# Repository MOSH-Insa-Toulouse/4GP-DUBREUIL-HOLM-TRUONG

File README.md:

# 4GP-DUBREUIL-HOLM-TRUONG

## SMOMAIRE
- [I) Présentation](#Présentation)
- [II) Matériel necessaire](#Matériel-necessaire)
   - [Software](#Software)
   - [Hardware](#Hardware)
- [III)Livrables](#Livrables)
   - [1) Simulation LtSpice](#Simulation-LtSpice)
   - [2) Conception PCB avec KiCad](#Conception-PCB-avec-KiCad)
   - [3) Code Arduino](#Code-Arduino)
   - [4) Application Android avec MITApp Inventor](#Application-Android-avec-MITApp-Inventor)
   - [5) Réalisation Physique du Circuit](#Réalisation-Physique-du-Circuit)
   - [6) Banc de Test Expérimental](#Banc-de-Test-Expérimental)
- [IV)Gestion de projet](#gestion-projet)
   - [1)Répartition du travail](#repartition-travail)
   - [2) Contacts](#contacts)

## I) Présentation
Ce répertoire présente l'ensemble des éléments nécessaire à la conception d'un capteur de pression en graphite réalisé dans le cadre de l'UF I4GPMH21 : Du capteur au banc de test en open source hardware.
L’objectif était de concevoir un dispositif de mesure de déformation utilisant un capteur innovant, low-tech, basé sur du graphite appliqué sur papier, selon le principe décrit dans l’article scientifique :  
**"Pencil Drawn Strain Gauges and Chemiresistors on Paper"** (Cheng-Wei Lin, Zhibo Zhao, Jaemyung Kim & Jiaxing Huang). Ce capteur, d'une simplicité remarquable, est constitué d'un morceau de papier sur lequel du graphite est appliqué à l'aide d'un crayon à papier.

Le principe de fonctionnement repose sur l'observation que la déformation du papier entraîne une variation du nombre de particules de graphite interconnectées. Cette modification de la structure granulaire du graphite se traduit par une variation de la résistance et de la conductance du capteur. En exploitant cette propriété, il devient possible de remonter à la déformation subie, à l'instar d'une jauge de contrainte classique.

Le fonctionnement repose sur la variation de la conductivité électrique du graphite en fonction de la contrainte mécanique appliquée au support papier. Ce phénomène permet de mesurer la déformation avec une technologie simple, accessible et écologique.
## II) Matériel necessaire
### ***Software*** (Présenté dans l'ordre d'utilisation)
1. LtSpice : Logiciel permettant la modélisation et simulation des circuits électroniques. 
1. KiCad : Logiciel permettant le développement et conception du PCB (*Printed Board Circuit*)
1. Arduino IDE : IDE utilisé pour écrire le code du micro-contrôleur Arduino. 
1. MITApp Inventor : WebService pour le développement d'une application Android.
### ***Hardware***
1. Micro-contrôleur Arduino UNO
1. Modules 
    * Bluetooth HC-05
    * Capteur de déformation en graphite
    * Capteur de déformation du commerce
    * Écran OLED
    * Encodeur Rotatoire
    * Potentiomètre digital
    * Servo-Moteur
1. Banc de test réalisé à l'imprimante 3D

## III) Livrables
### 1) Simulation LtSpice

Un montage à transimpédance a été conçu afin d'amplifier le faible courant produit par le capteur graphite. Ce montage utilise un amplificateur opérationnel de précision (LTC1050) pour convertir le courant en tension, compatible avec les entrées analogiques d’un Arduino UNO.  

Trois filtres passe-bas ont été intégrés pour minimiser le bruit :
- Un filtre passe-bas passif (R1, C1) à l'entrée : filtre RC à 16 Hz pour réduire les perturbations en courant,
- Un filtre passe-bas actif (R3, C4) couplé à l'AOP : filtre actif à 1,6 Hz pour éliminer le bruit secteur (50 Hz),
- Un filtre passe-bas (R5, C2) à la sortie de l'AOP : filtre à 1,6 kHz pour lisser le signal final.

Des simulations transitoires et fréquentielles ont validé l’amplification et l’efficacité de la filtration (atténuation > 70 dB à 50 Hz).

#### ***Graphique***

#### ***Schéma du montage***

### 2) Conception PCB avec KiCad

Dans cette section, nous présentons le processus de conception du circuit imprimé du projet, allant de la simulation électrique à la modélisation 3D, en passant par le routage des composants. L’objectif est de réaliser une carte fonctionnelle permettant l’acquisition, le traitement et la transmission du signal mesuré par le capteur graphite.

### Étape 1 : Sélection et intégration des composants

Le circuit est conçu pour intégrer et connecter plusieurs composants essentiels à l’Arduino :

- Amplificateur opérationnel **LT1050** (amplification analogique du signal capteur)
- **Servomoteur** 
- **Potentiomètre numérique** (ajustement dynamique de gain)
- **Encodeur rotatoire**
- **Écran OLED**
- **Module Bluetooth HC-05** (communication sans fil avec une application mobile)
- Deux broches dédiées au **capteur graphène**

L’ensemble des connexions logiques et électriques est établi dans le schéma du PCB sur KiCad pour s'assurer de la compatibilité avec l’Arduino.

### Étape 2 : Simulation du schéma électrique

La conception a débuté par la création d’un schéma électrique simulé sous **LTspice**. Cette simulation permet de valider le comportement du circuit d’amplification, notamment autour de l’amplificateur opérationnel **LT 1050**, qui joue un rôle essentiel dans l’amplification du signal analogique issu du capteur graphite.

Une fois le schéma validé, il est reproduit dans **KiCad** afin de préparer la conception physique du circuit.

#### ***Schematic***

Ici sont présenté les différents éléments qui composeront le *shield* de notre projet ainsi que l'assignation des différentes connexions. On y retrouve en haut à droite l'ensemble des pins de connexion de l'arduino, à gauche, le schéma de l'amplificateur ainsi que la connexion du capteur graphène. Enfin, en bas, on retrouve la schématisation des différents modules à intégrer.

### Étape 3 : Routage PCB dans KiCad

La phase suivante consiste à réaliser le **routage** du circuit. Cela implique de placer les composants sur le PCB, de définir les couches, les largeurs de piste et les zones de masse, puis de relier chaque broche selon le schéma précédent.

L’objectif est d’optimiser la compacité, de limiter les interférences et d’assurer la robustesse du signal analogique.

**Aperçu du PCB routé :**

---

### Étape 4 : Visualisation 3D

Une fois le routage terminé, **KiCad** permet de générer un **modèle 3D** réaliste de la carte. Cette vue permet de vérifier l’encombrement, l’orientation des composants, et de prévoir les contraintes mécaniques ou d’intégration dans un boîtier physique.

**Modélisation 3D du PCB :**

---
### 3) Code Arduino
Le code Arduino doit permettre la réalisation des fonctions suivantes :
1. Récupérer les données du capteur graphène fait main
1. Naviguer dans un menu avec l'encodeur rotatoire et afficher sur l'écran OLED.
1. Gérer les valeurs de résistance du potentiomètre digital
1. Définir l'action du servo-moteur

Pour accomplir toutes ces actions, l'ensemble des fonctionnalités est géré à partir d'un menu à plusieurs niveau construit sur le modèle d'une machine à état.
Ainsi, dans le code deux fonctions sont construites pour gérer les mouvements de l'encodeur rotatoire et la gestion des menus.
L'arborescence finale du menu est construite comme suit : 
- Resistance R2
- Servo-moteur
   - Pousser
      - Angle 30
      - Angle 45
      - Angle 60
      - Angle 90
      - Retour
   - Tirer
      - Angle 30
      - Angle 45
      - Angle 60
      - Angle 90
      - Retour
   - Retour

Une fois l'angle selectionné, le mouvement du servo-moteur se déclenche et la mesure est réalisée (voir partie banc de test) 

---
### 4) Application Android avec MITApp Inventor

Nous avons développé une application Android avec **MIT App Inventor**. Cette application doit permettre la communication sans fil avec le module Bluetooth présent sur le *shield*, afin de visualiser les données du capteur en temps réel sur un téléphone android par exemple.

#### Objectifs

- Établir une connexion Bluetooth entre le smartphone Android et le module Arduino.
- Afficher la résistance du **potentiomètre digital** ainsi que celle du **capteur graphène**.
- Tracer une courbe en temps réel représentant l’évolution de la résistance du capteur.

#### Interface utilisateur

- Le bouton **Bluetooth** permet de se connecter au module Arduino via Bluetooth.
- Une fois connecté, le bouton change de couleur en **vert** et affiche l'état **Connected**.
- Pour se déconnecter, il suffit d'appuyer sur le bouton **Kicad**.
- Au centre de l'écran, un graphique affiche en temps réel la résistance mesurée du capteur graphène.
- En bas de l'écran, deux valeurs sont affichées :
  - La valeur de la résistance du **potentiomètre digital** séléctionnée
  - La valeur de la résistance instantanée du **capteur graphène**

#### Blocs MIT App Inventor

L'application utilise des blocs pour :

- Établir la connexion Bluetooth
- Recevoir les données depuis l'Arduino via UART
- Traiter les données reçues et les afficher dans un graphique
- Mettre à jour l'interface en fonction de l'état de la connexion

Voici une image représentant les blocs utilisés dans le projet :

---
### 5) Réalisation Physique du Circuit

Le circuit final a été soudé et testé dans les laboratoires du département. Des tests ont confirmé la stabilité du signal et l’efficacité des différents modules. Les soudures ont été réalisées manuellement pour garantir une bonne qualité de connexion.

---
### 6) Banc de Test Expérimental

Le banc de test qui nous a permis de réaliser l'expérience a été developpé avec le logiciel **Fusion 360**. 
Il est composé de :
1. Un support pour le micro-contrôleur Arduino
1. Un support pour le servo moteur
1. Un bras pour lié le servo-moteur au mobile
1. Un rail 
1. Un mobile 
1. Un support pour le capteur graphène.

L'ensemble de ces pièces sont à retrouver dans le dossier "Banc de test" ainsi que la vue globale présentée plus bas.

L'idée de ce banc de test est de courber le papier à l'aide du mobile qui sera actionner par le servo-moteur. Pour avoir un ensemble de mesure à réaliser le micro-contrôleur gère l'angle de la course imposé au moteur. Ainsi, on peut raisonnablement penser que pour un même angle de course appliqué, le capteur subira toujours la même déformation. 

Les courbes de mesure à établir seront donc la variation de résistance suivant la course faite par le mobile

Une fois le banc installé, il n'y a plus qu'à naviguer dans le menu affiché sur l'écran OLED à l'aide de l'encodeur rotatoire pour choisir la direction du mouvement et l'inclinaison. Une fois ces paramètres séléctionné par l'utilisateur, le resultat s'affiche dans le *Serial Monitor* ici Teleplot.

---
## Gestion du Projet
### 1) Répartition du travail
Au cours de ce projet, il a été necessaire de se répartir le travail pour couvrir le maximum de points importants. En cas de questions pour les futurs lecteurs ne pas hésiter à contacter les personnes sur leur différents points.
Ainsi, les tâches ont été réparties comme suit : 

- DUBREUIL Pierrick
   - KiCad : 
      - Réalisation du plans *schematic*
      - PCB : Correction d'empreintes + Routage des pistes
   - Banc de test 3D : 
      - Conception des différents éléments du banc sur Fusion 360
      - Impression des éléments du banc
   - Code Arduino : 
      - Construction du menu global
      - Gestion des commandes du servo-moteur
      - Acquisition des données du capteur graphène et affichage
- HOLM Ane-Marie
   - Développement du *front-end* de l'application Android
   - Rédaction de la *datasheet* du capteur
- TRUONG Nguyen 
   - KiCad :
      - Création d'empreintes PCB
      - Correction routage des pistes
      - Rendu 3D final
   - Code Arduino
      - Gestion de la résistance du potentiomètre digital
   - MITAPP :
      - Conception de l'application

---
### 2) Contacts
[DUBREUIL Pierrick](https://github.com/pierrickdubreuil17)(pdubreuil@insa-toulouse.fr)

[HOLM Anne-Marie](https://github.com/anemho)

[TRUONG Nguyen Gia Khanh](https://github.com/ntruonginsatls) (ntruong@insa-toulouse.fr)

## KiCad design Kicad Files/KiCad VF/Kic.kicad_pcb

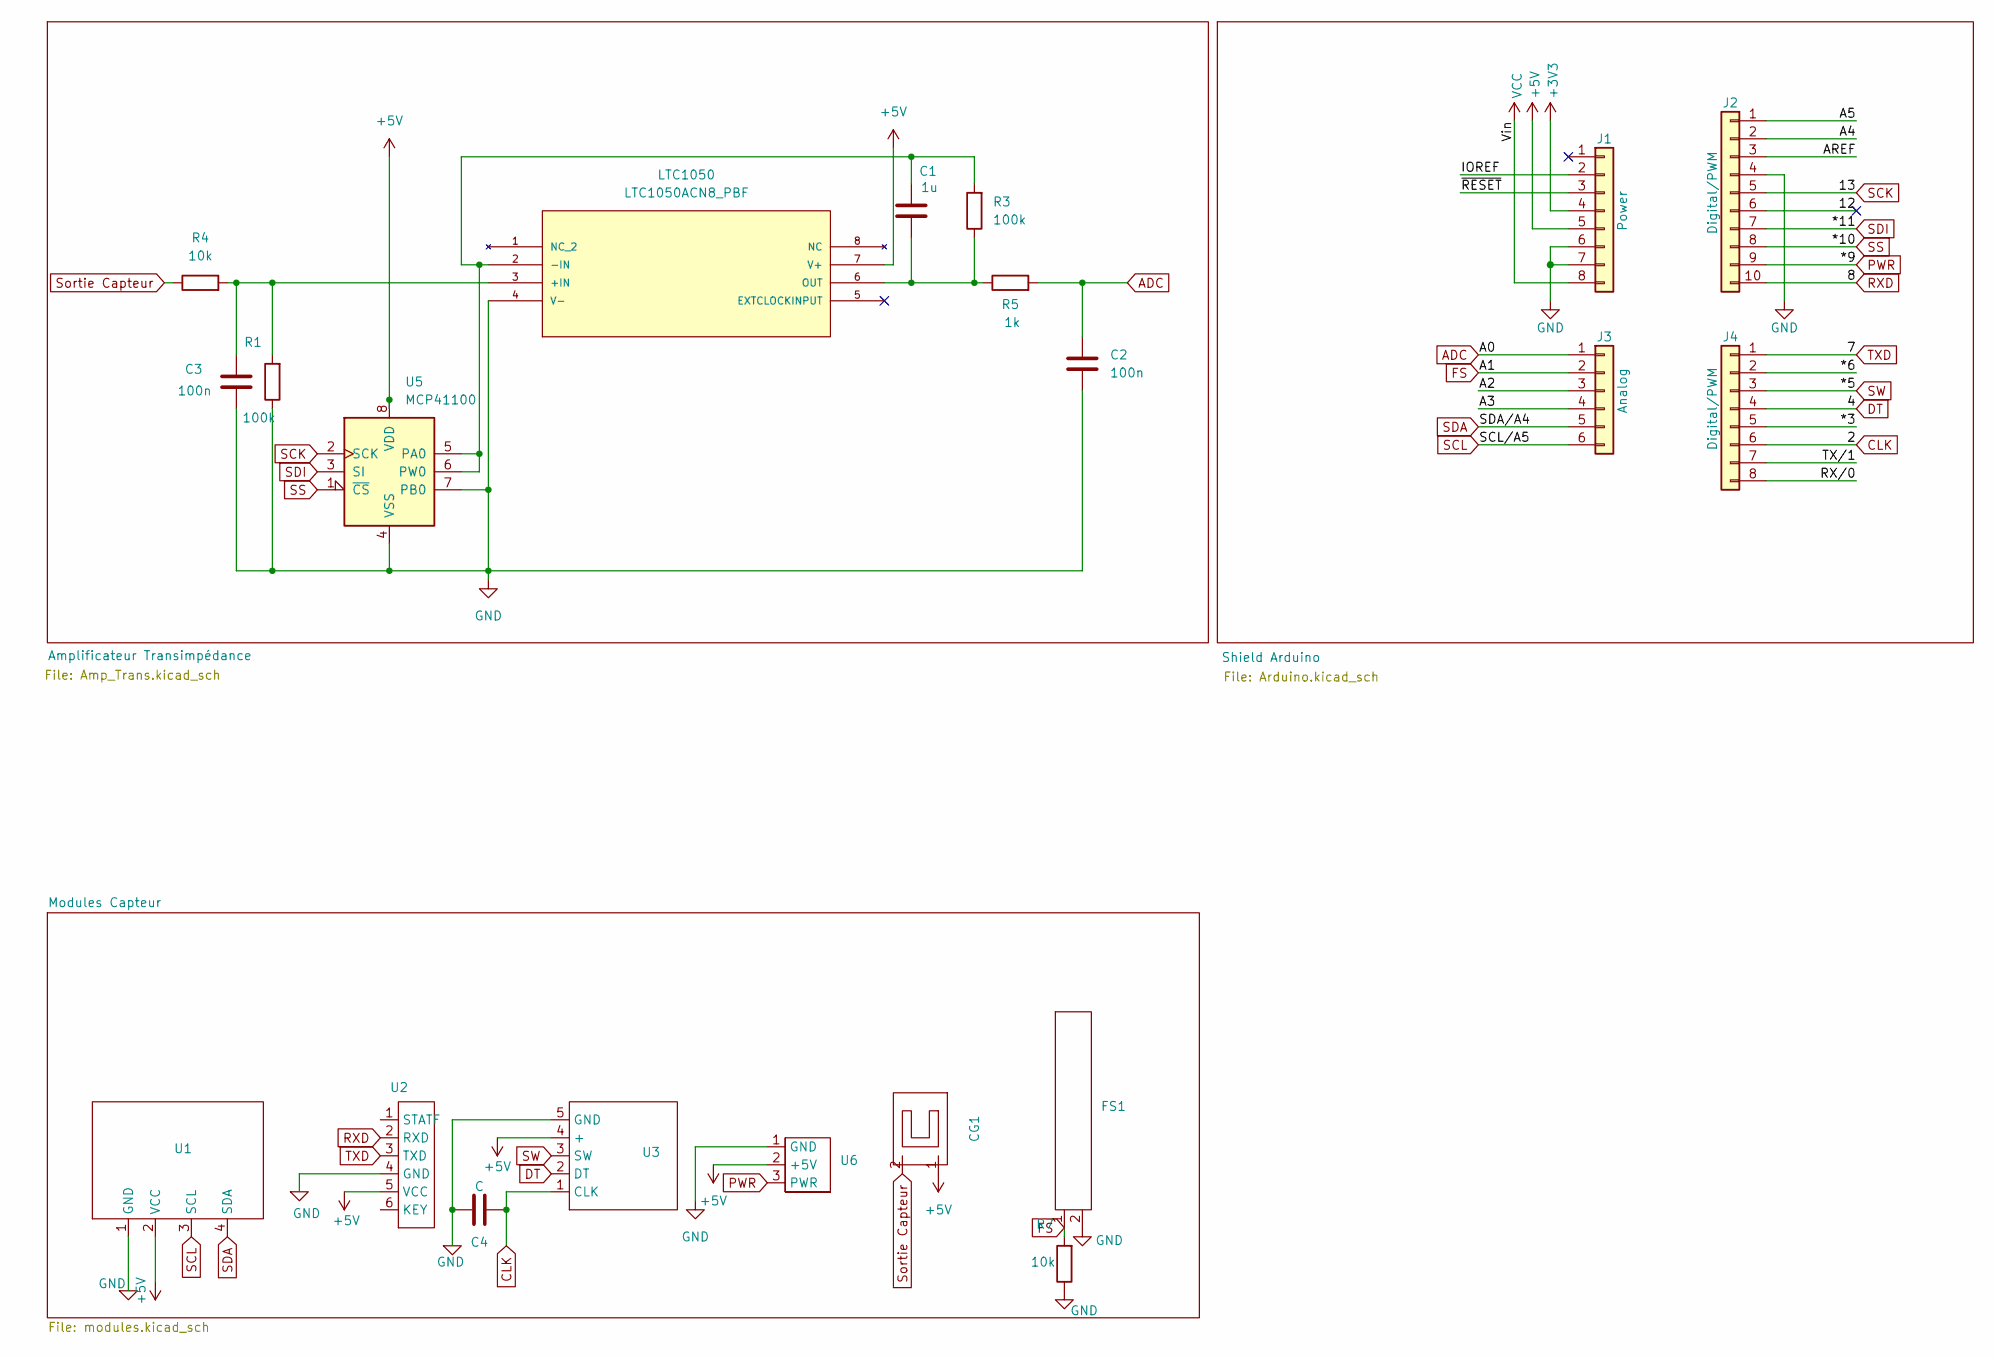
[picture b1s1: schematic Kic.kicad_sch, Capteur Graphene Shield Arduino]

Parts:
C1: 1u; C_Rect_L7.2mm_W5.5mm_P5.00mm_FKS2_FKP2_MKS2_MKP2
C2, C3: 100n; C_Disc_D4.3mm_W1.9mm_P5.00mm
C4: C; C_Disc_D4.3mm_W1.9mm_P5.00mm
CG1: SIP-2
FS1: SIP-2
J1: Power; PinSocket_1x08_P2.54mm_Vertical
J2: Digital/PWM; PinSocket_1x10_P2.54mm_Vertical
J3: Analog; PinSocket_1x06_P2.54mm_Vertical
J4: Digital/PWM; PinSocket_1x08_P2.54mm_Vertical
LTC1050: LTC1050ACN8_PBF; PDIP-8_N; MANUFACTURER_PART_NUMBER ltc1050acn8
R1, R3: 100k; R_Axial_DIN0204_L3.6mm_D1.6mm_P5.08mm_Horizontal
R4, R7: 10k; R_Axial_DIN0204_L3.6mm_D1.6mm_P5.08mm_Horizontal
R5: 1k; R_Axial_DIN0204_L3.6mm_D1.6mm_P5.08mm_Horizontal
U1: SIP-4
U2: BLUETOOTH2
U3: ENCODEUR ROTATION
U5: MCP41100; MCP4110
U6: ServomoteureHeader

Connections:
+3V3: J1.4
+5V: CG1.1, J1.5, LTC1050.7 (V+), U1.2 (VCC), U2.5 (VCC), U3.4 (+), U5.8 (VDD), U6.2 (+5V); also elsewhere on the board
/12: J2.6
/*3: J4.5
/*6: J4.2
/A2: J3.3
/A3: J3.4
/A4: J2.2
/A5: J2.1
/AREF: J2.3
/IOREF: J1.2
/RX/0: J4.8
/TX/1: J4.7
/~RESET: J1.3
ADC: C2.1, J3.1, R5.2
CLK: C4.2, J4.6, U3.1 (CLK); also elsewhere on the board
DT: J4.4, U3.2 (DT); also elsewhere on the board
FS: FS1.1, J3.2, R7.2
GND: C2.2, C3.1, C4.1, FS1.2, J1.6, J1.7, J2.4, LTC1050.4 (V-), R1.1, R7.1, U1.1 (GND), U2.4 (GND), U3.5 (GND), U5.4 (VSS), U5.7 (PB0), U6.1 (GND); also elsewhere on the board
unnamed: C3.2, LTC1050.3 (+IN), R1.2, R4.2
unnamed: C1.1, LTC1050.2 (-IN), R3.2, U5.5 (PA0), U5.6 (PW0)
unnamed: C1.2, LTC1050.6 (OUT), R3.1, R5.1
PWR: J2.9, U6.3 (PWR)
RXD: J2.10, U2.2 (RXD); also elsewhere on the board
SCK: J2.5, U5.2 (SCK)
SCL: J3.6, U1.3 (SCL)
SDA: J3.5, U1.4 (SDA)
SDI: J2.7, U5.3 (SI)
SS: J2.8, U5.1 (~CS)
SW: J4.3, U3.3 (SW); also elsewhere on the board
Sortie Capteur: CG1.2, R4.1
TXD: J4.1, U2.3 (TXD); also elsewhere on the board
VCC: J1.8

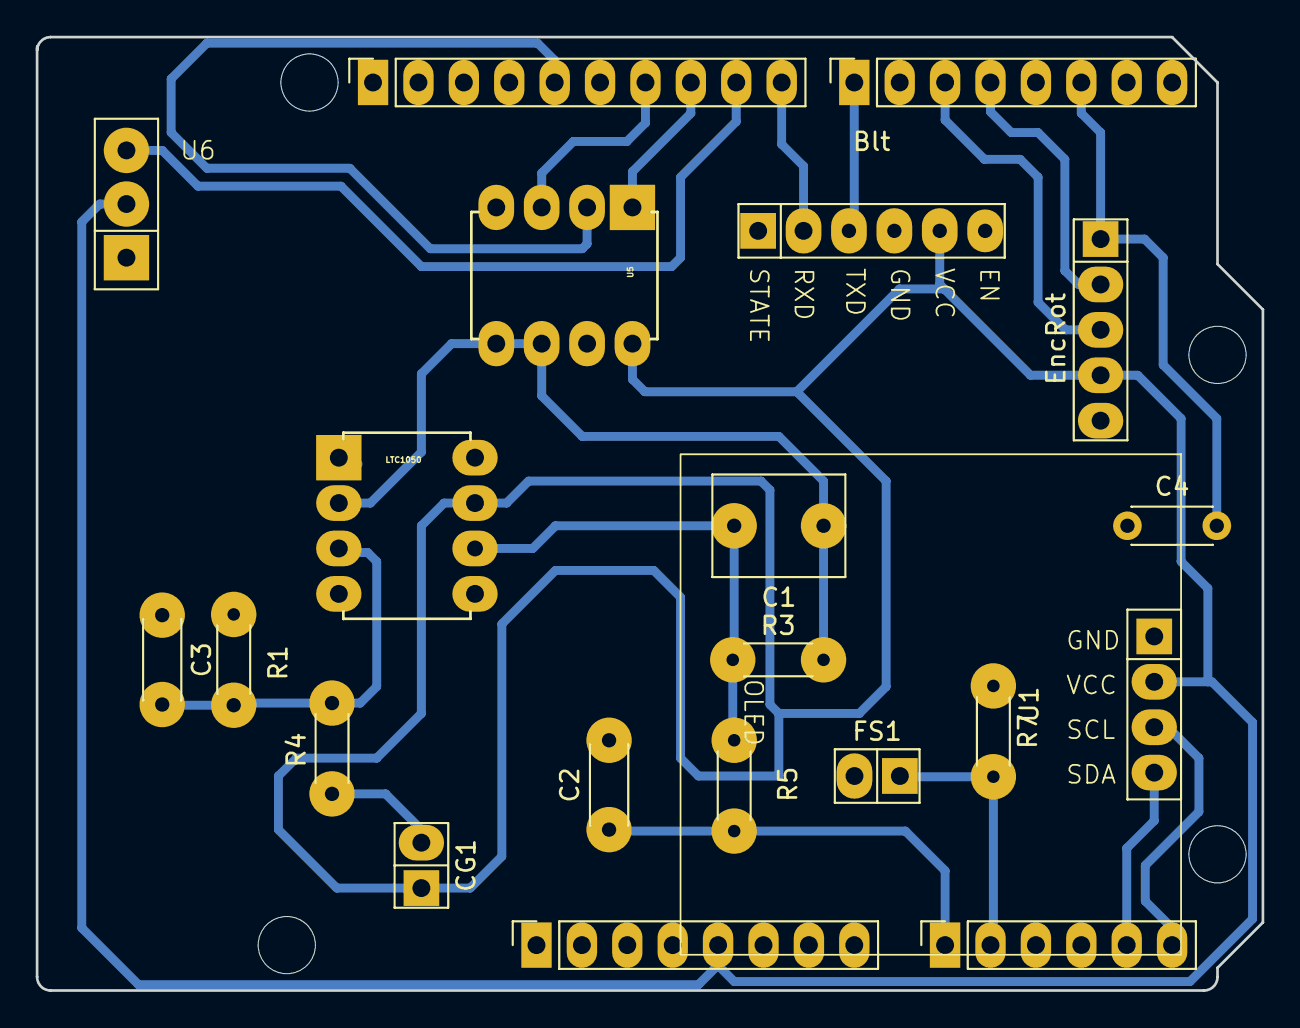
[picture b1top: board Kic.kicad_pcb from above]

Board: 2 copper layers, 68.6 x 53.3 mm, 25 parts (0 on the bottom side), 19 nets.

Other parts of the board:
Blt: BLUETOOTH2
EncRot: ENCODEUR ROTATION
MH1, MH2, MH3, MH4: MountingHole_3.2mm

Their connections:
+5V: Blt.5 (VCC), EncRot.4 (+); also elsewhere on the board
CLK: EncRot.1 (CLK); also elsewhere on the board
DT: EncRot.2 (DT); also elsewhere on the board
GND: Blt.4 (GND), EncRot.5 (GND); also elsewhere on the board
RXD: Blt.2 (RXD); also elsewhere on the board
SW: EncRot.3 (SW); also elsewhere on the board
TXD: Blt.3 (TXD); also elsewhere on the board

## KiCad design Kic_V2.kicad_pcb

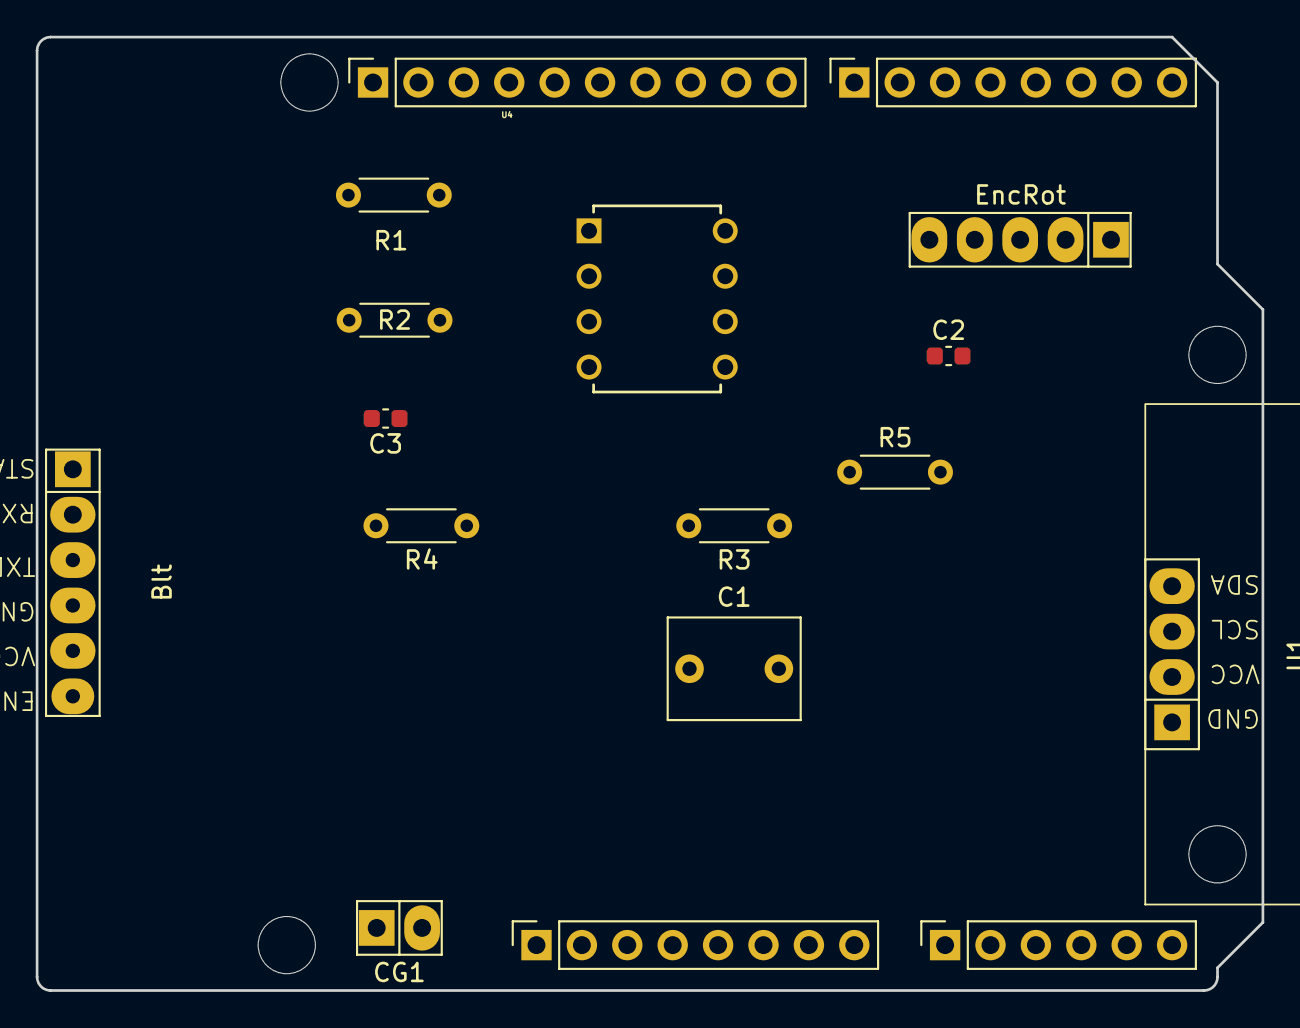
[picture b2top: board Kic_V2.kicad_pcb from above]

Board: 2 copper layers, 68.6 x 53.3 mm, 21 parts (0 on the bottom side), 13 nets, no tracks yet.

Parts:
Blt: BLUETOOTH2
C1: 1u; C_Rect_L7.2mm_W5.5mm_P5.00mm_FKS2_FKP2_MKS2_MKP2
C2, C3: 100n; C_0603_1608Metric
CG1: SIP-2
EncRot: ENCODEUR ROTATION
J1: Power; PinSocket_1x08_P2.54mm_Vertical
J2: Digital/PWM; PinSocket_1x10_P2.54mm_Vertical
J3: Analog; PinSocket_1x06_P2.54mm_Vertical
J4: Digital/PWM; PinSocket_1x08_P2.54mm_Vertical
MH1, MH2, MH3, MH4: MountingHole_3.2mm
R1, R3: 100k; R_Axial_DIN0204_L3.6mm_D1.6mm_P5.08mm_Horizontal
R2, R5: 1k; R_Axial_DIN0204_L3.6mm_D1.6mm_P5.08mm_Horizontal
R4: 10k; R_Axial_DIN0204_L3.6mm_D1.6mm_P5.08mm_Horizontal
U1: SIP-4
U4: LTC1050ACN8_PBF; PDIP-8_N

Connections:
+5V: Blt.5 (VCC), CG1.1, EncRot.4 (+), J1.5, U1.2 (VCC), U4.7 (V+)
ADC: C2.1, R5.2
CLK: EncRot.1 (CLK), J4.6
DT: EncRot.2 (DT), J4.4
GND: Blt.4 (GND), C2.2, C3.1, EncRot.5 (GND), J1.6, J1.7, J2.4, R1.1, R2.1, U1.1 (GND), U4.4 (V-)
unnamed: CG1.2, R4.1
unnamed: C1.1, C3.2, R1.2, R2.2, R3.2, R4.2, U4.2 (-IN), U4.3 (+IN)
unnamed: C1.2, R3.1, R5.1, U4.6 (OUT)
RXD: Blt.2 (RXD), J2.8
SCL: J2.1, J3.6, U1.3 (SCL)
SDA: J2.2, J3.5, U1.4 (SDA)
SW: EncRot.3 (SW), J4.3
TXD: Blt.3 (TXD), J4.1

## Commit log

2025-03-12 Test de commit 1
2025-03-12 Ajout des dossiers pour l'arborescence du projet
2025-03-12 Test by Ane
2025-03-12 Deleting test folder
2025-03-12 Ajout de datasheet
2025-03-12 Test add folder
2025-03-12 Added folder to test
2025-03-12 Adding document in folder to test
2025-03-12 ajoute fichier KiCad
2025-03-12 ajoute lib
2025-03-13 Ajout des fichiers dans le dossier Kicad Files
2025-03-13 Nouvelle version des fichiers kicad
2025-03-13 Ajout du travail réalisé pendant la séance du 13.03+ Correction des pistes et ajout header servo-moteur
2025-03-16 Ajout d'une V5 des fichiers Kicadet mise à jour du fichier Arduino avvec l'ajout de code pour les différents modules
2025-03-16 Ajout des bibliothèques perso de Pierrick et déplacement des bibliothèques de Nguyen dans le dossier Kicad files
2025-03-17 Modification d'attribution de pins
2025-03-21 Ajout de la nouvelle version du PCB
2025-03-22 Retravaille des pistes du PCB : Pose d'un via et vérification du plan de masse
2025-03-22 MOdif .Ds_Store
2025-03-22 Ajout de .DS_Store dans .gitignore
2025-03-22 Suppression de .DS_Store du dépôt
2025-03-22 Ajout de .DS_Store dans .gitignore et suppression du suivi
2025-03-25 Modification des dossiers suite à la réalisation du PCB
2025-03-25 Modification du dossier Module 3D
2025-03-25 3D Changement
2025-03-25 Modification du fichier Readme.md
2025-03-25 Modification du Readme.md
2025-03-25 Ajout de la section "Arduino" dans le Readme.md
2025-03-25 Modification de la section "Contacts"
2025-03-27 Test Images Readme.md
2025-03-27 Test_2 Images
2025-03-27 Test 3 Image
2025-03-27 Ajout image Kicad
2025-03-27 Ajout du schema LtSpice
2025-03-27 Ajout du texte Arduino dans le Readme
2025-03-28 Changement dans la rubrique contact du Readme
2025-03-28 Ajout du dossier Android App
2025-03-28 Ajout test.txt
2025-03-28 Ajout du fichier Projet capteur.apk
2025-04-02 Ajout de la fonction de lecture du capteur dans l'arduino + Suppression de fichiers doublons
2025-04-03 mettre a jour code arduino
2025-04-07 Point de départ du travail sur le code arduino
2025-04-07 Ajout du code BT
2025-04-08 Ajout des fonctions du module Bt et Servo moteur
2025-04-09 Frontend app
2025-04-23 Mise à jour du code arduino
2025-04-23 Ajout de docstrings
2025-04-23 Ajout de docstring
2025-04-23 Mise au propre du dossier Arduino Files
2025-04-23 Suppression des doublons
2025-04-23 Ajouts des fichiers 3D pour le band de Test
2025-05-20 Modification du code arduino
2025-05-20 ModificatIon du code
2025-05-20 Fin de la fonction de navigation pour le servo moteur
2025-05-22 Fin code arduino
2025-05-22 gestion menu ok
2025-05-29 Mise à jour du Read.me + ajout du dossier contenant les documents pour la soutenance finale
2025-05-29 Ajout de l'image banc de test dans le readme
2025-05-29 Ajout image Teleplot
2025-05-29 Ajout image serial
2025-05-29 upload image
2025-05-29 Update image
2025-05-30 Ajout du descriptif des fonction du code dans le readme
2025-05-30 Mise au propre des fichiers Github
2025-05-30 Modification image banc test
2025-05-30 Correction image readme
2025-05-30 Ajout de la section Répartition du travail
2025-05-30 modification répartition
2025-05-30 Mise à jour sommaire
2025-05-30 ajout tâche
2025-05-30 Version finale Readme

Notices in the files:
parts and their libraries:
COPYRIGHT: Copyright C 2016 Accelerated Designs. All rights reserved
